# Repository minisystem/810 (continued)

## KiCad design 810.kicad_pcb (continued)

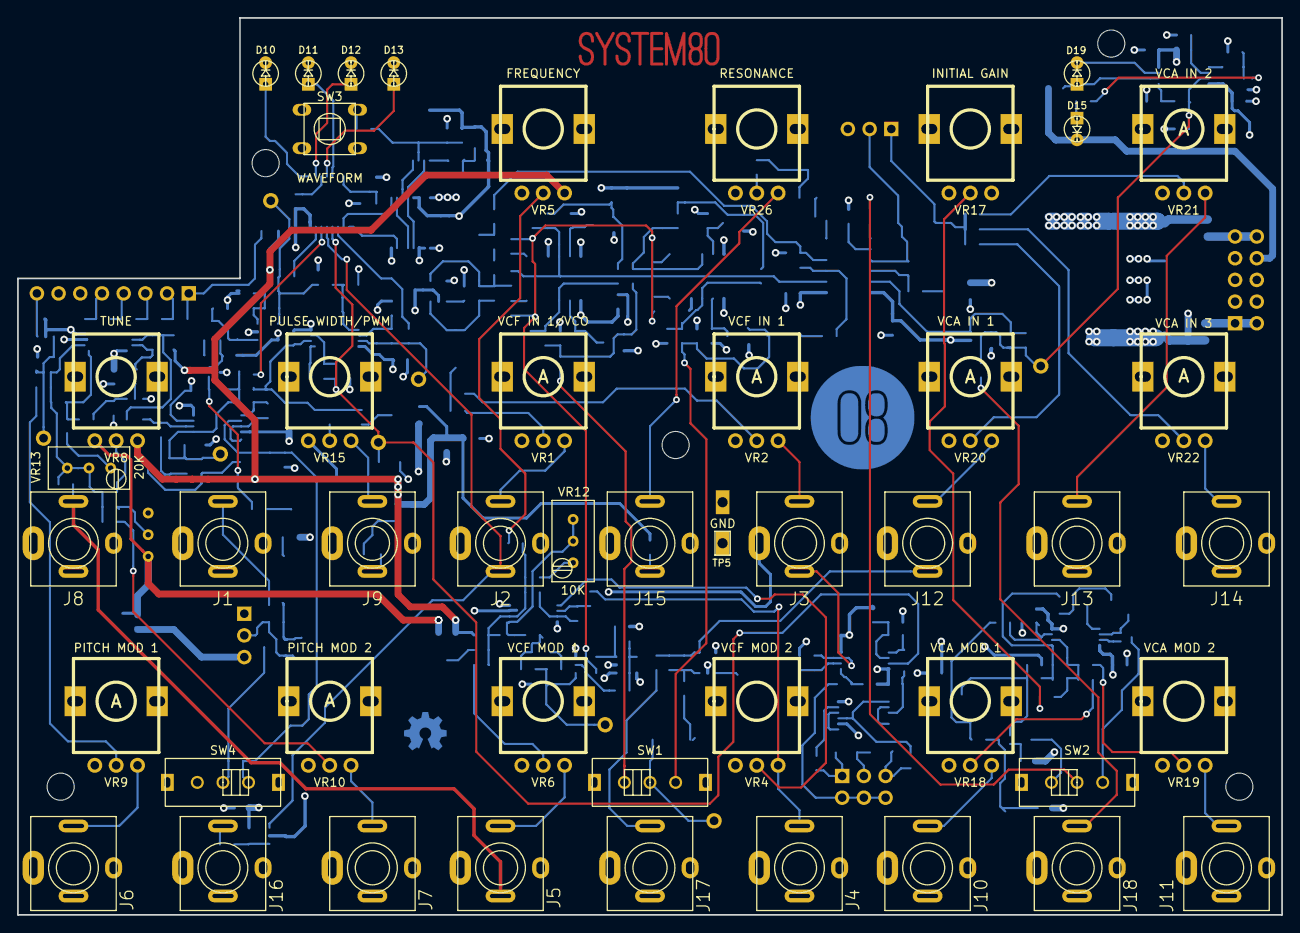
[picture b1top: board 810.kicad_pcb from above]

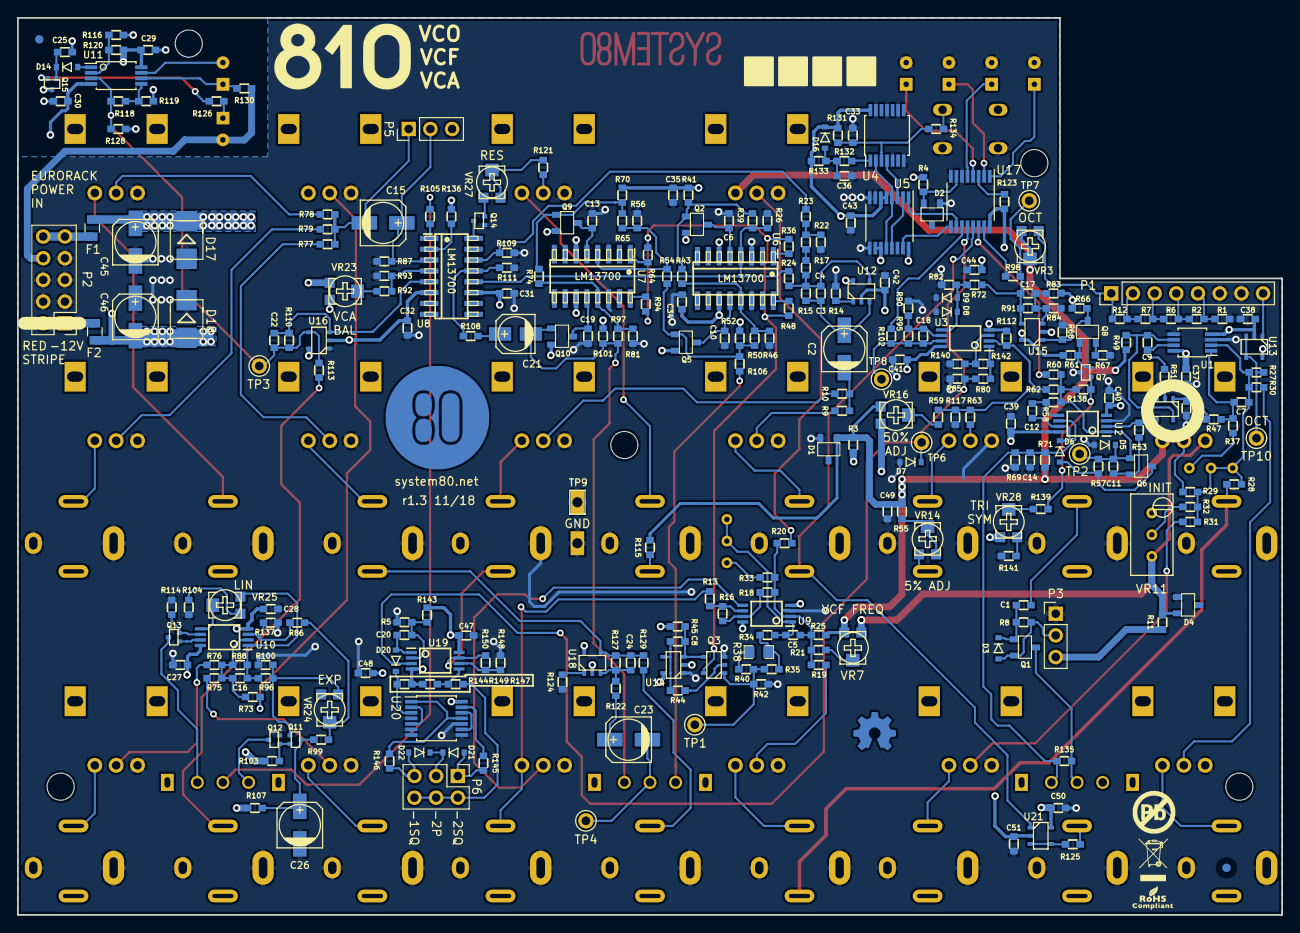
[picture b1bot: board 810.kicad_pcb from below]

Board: 4 copper layers, 148.0 x 105.0 mm, 331 parts (279 on the bottom side), 197 nets.

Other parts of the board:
C14: 10n; SM0603-C-MURATA
SNAP-HOLE-0.125-INCH, SNAP-HOLE-0.125-INCH#2, SNAP-HOLE-0.125-INCH#3, SNAP-HOLE-0.125-INCH#4, SNAP-HOLE-0.125-INCH#5: VAL**; SNAP_HOLE_0.125_INCH

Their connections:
SYNC: C14.1; also elsewhere on the board

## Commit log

2017-07-17 changed to Toshiba matched pairs, added 12dB/24dB selector switch
2017-07-18 gibber jabber
2017-07-19 added panel file from ubuntu mac
2017-08-22 finishing off, tidying up
2017-08-23 added bi-color LED level indicator circuit
2017-09-01 annotated and ERC done
2017-09-25 panel update from mac pro
2017-09-25 pcbnew file created, pots/jacks/switches placed
2017-09-26 added hard/soft sync switch
2017-10-13 updated SW1 rotary switch footprint to Alpha SR2511
2017-10-20 latest panel update
2017-10-23 started PCB part placement
2017-10-29 more part placement. done VCO and VCF, started VCA
2017-11-03 added rotary switch, integrated into main PCB
2017-11-05 routing
2017-11-06 main power rails routed
2017-11-06 placed and routed previously unplaced C7
2017-11-11 all components placed, mostly routed
2017-11-12 routed, yo
2017-11-19 changed a bunch of wrong footprints and added gitignore
2017-11-21 finesse references, ongoing
2017-11-22 more silkscreen work
2018-01-15 changes to schematic for next revision, not yet implemented in PCB
2018-01-16 schematic changes updated in PCB, routed
2018-01-17 more routing and tweaking. Still need to change 2SK208 footprints
2018-01-22 added secret sub-oscillator
2018-01-23 board tweaking, getting ready to match up with panel art and order second prototype
2018-01-25 changes switches to horizontal position
2018-01-25 panel updates from mac pro
2018-01-26 ordered PCB v1-1
2018-02-13 panel backup from Mac-Pro
2018-02-17 couple of changes to schematic to reflect updated part values in r1.1 build
2018-02-20 more notes from v1.1 build. sync reset problem with C14 fixed
2018-02-21 panel update from MacPro
2018-02-21 sync from Mac Pro
2018-02-21 update from PC with hopefully fixed dxf mechanical
2018-02-22 fixed position of middle switch, offset by 0.5 mm
2018-02-22 update from mac pro
2018-02-23 updated dimensioned 810 panel drawing"
    a
2018-04-24 ground plane stiching and tweaking
2018-04-26 changed TRI and SINE waveshapers - tested and working
2018-04-28 beefed up rail traces, replaced pwm rail references with +10V ref
2018-04-28 bit more silk screen tweaking, then 2 layer version is done
2018-04-29 4 layer version amost done with dedicated ground plane and power plane
2018-04-30 little more ground plane tweaking required, tidy up silk screen then done
2018-04-30 moved rotary switch to its own PCB
2018-04-30 moved rotary switch to its own 2-layer PCB
2018-05-07 bit of tweaking. ready to order
2018-06-19 added readme, updated schematic based on 4layer build
2018-06-19 added readme
2018-09-07 couple of notes added and changed in schematic
2018-09-10 changed a couple of schematic notes
2018-09-27 separate LED ground path
2018-10-04 0603 R and C footprints swapped for reflow friendly footprints
2018-10-05 prep for panelization. swapping pot footprints for better mounting lug hole fit
2018-10-08 tweaks. about to panelize
2018-10-09 panelized
2018-10-13 changed U1 from TSSOP to MSOP on panel. grrrr
2018-11-08 meh. gonna change matched pair and repanelize
2018-11-09 updated matched pair to PMP4201
2018-11-14 merbheh. PMP4201 in there, 2SC4207 on the front as a back up, but going to revert back to 2sC4207 as one and only NPN pair. indecision is killing me.
2018-11-14 reverted back to 2SC4207 and single tempco in divider
2018-11-14 more tweaking of unit PCB. about to re-panelize
2018-11-15 re-panelized and rfq sent to Ivan
2019-04-07 manual updates from Mac Pro
2019-04-10 user guide updates
2019-04-10 changes to PCB to update mistakes in BOM
2019-04-10 test
2019-04-13 more 810 manual work
2019-04-23 user manual update from mac pro
